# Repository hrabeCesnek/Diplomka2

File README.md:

# Diplomka
Nothing more than destiny fullfillation

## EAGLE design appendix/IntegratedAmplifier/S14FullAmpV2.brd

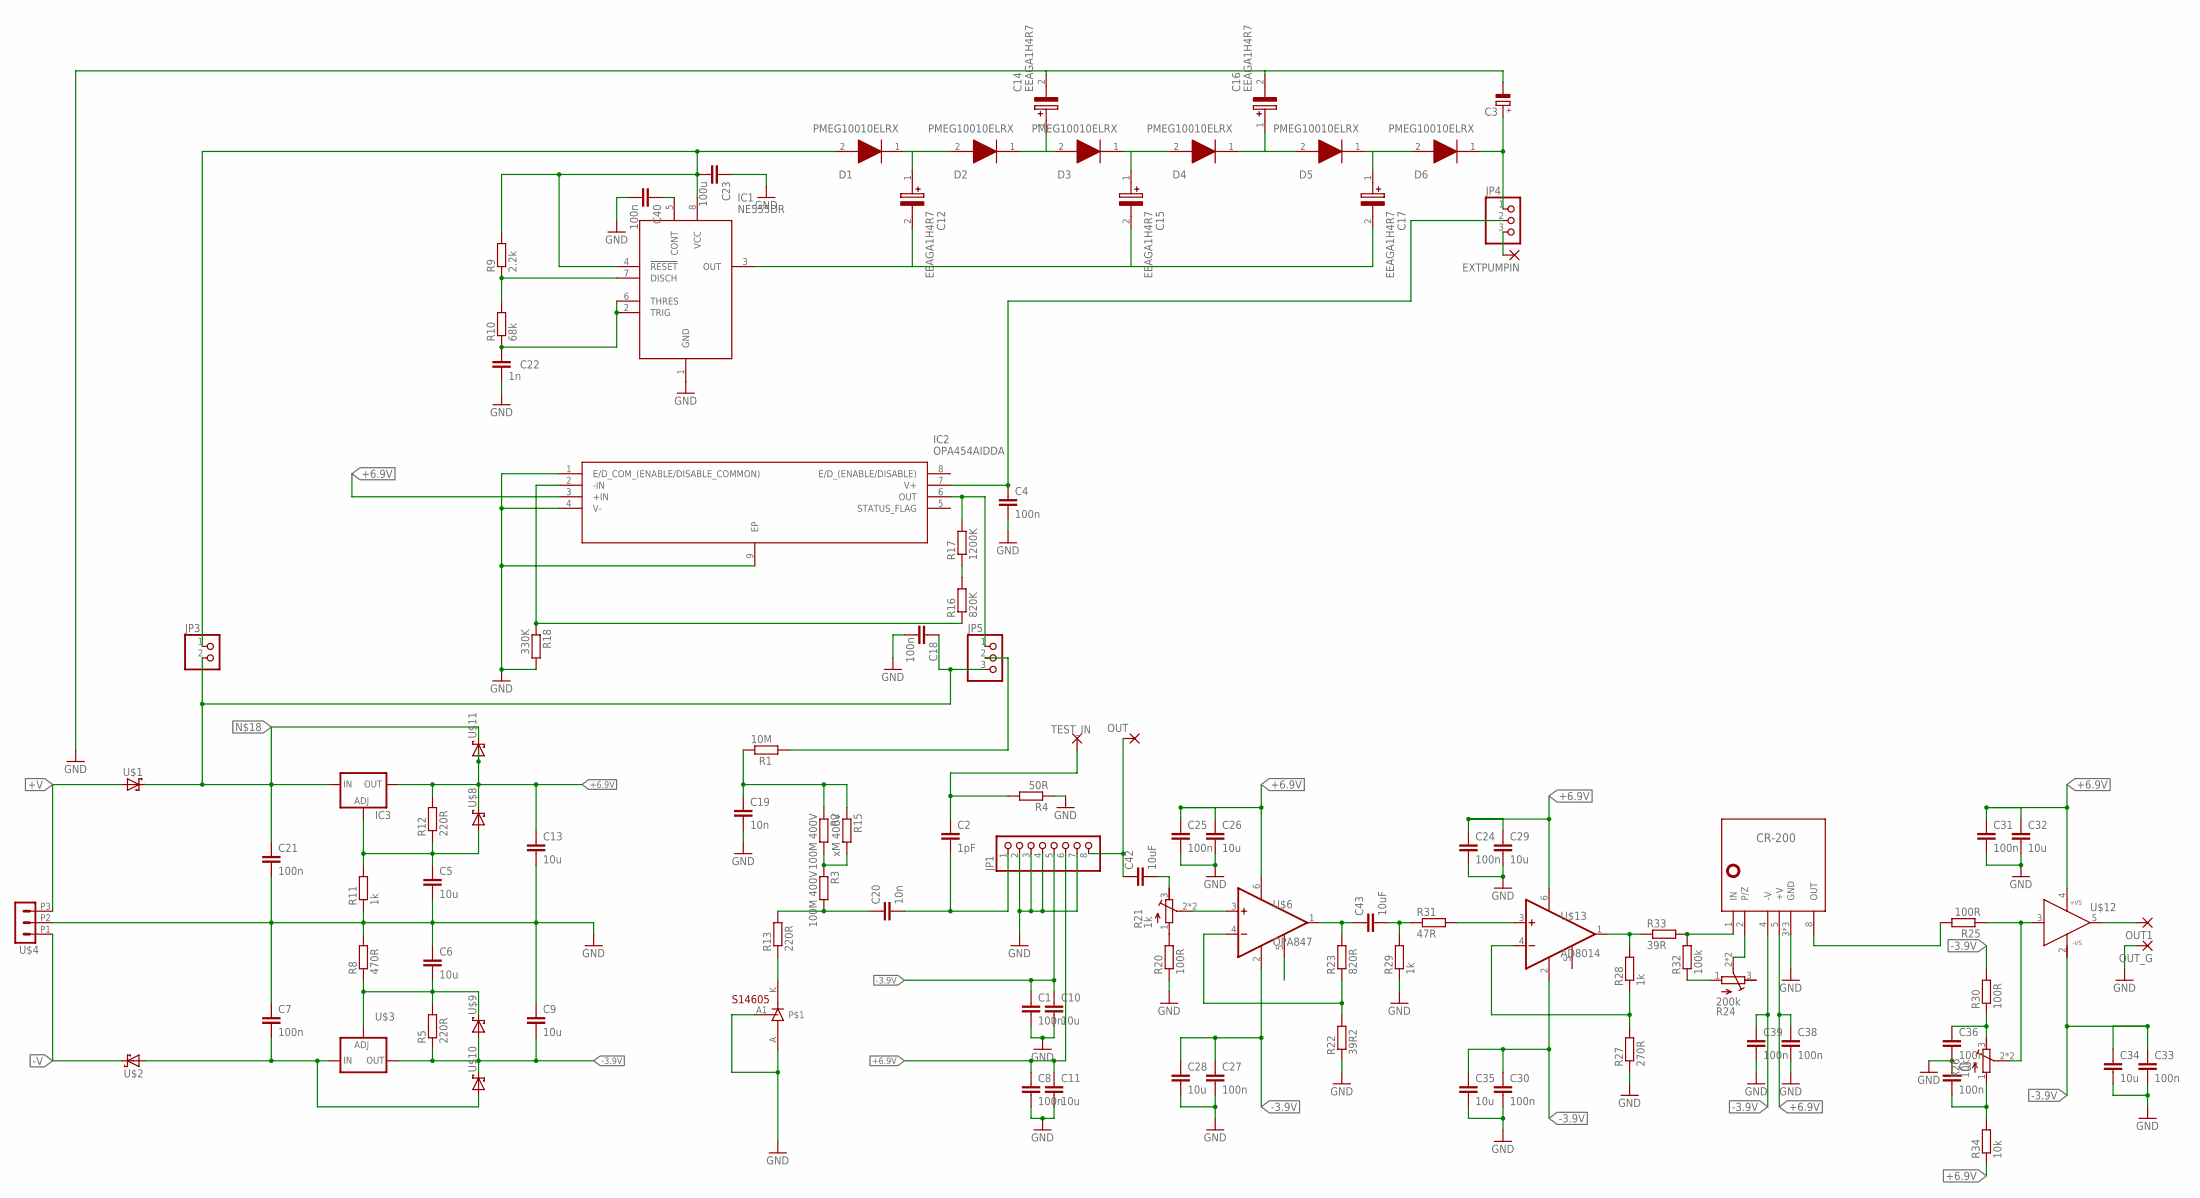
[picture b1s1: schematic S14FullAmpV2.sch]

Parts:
C1, C4, C7, C8, C18, C21, C24, C25, C27, C30, C31, C33, C36, C37, C38, C39, C40: 100n; C0603
C2: 1pF; C0603
C3: CPOL-EUE3.5-8; E3,5-8
C5, C6, C9, C10, C11, C13, C26, C28, C29, C32, C34, C35: 10u; C0805
C12, C14, C15, C16, C17: EEAGA1H4R7; CAPPRD150W50D400H800
C19, C20: 10n; C0603
C22: 1n; C0603
C23: 100u; C0603
C42, C43: 10uF; C0805
CR-200: CR-200H; CR-XXX-H
D1, D2, D3, D4, D5, D6: PMEG10010ELRX; SODFL3517X110N
EXTPUMPIN: 1,6/0,9
IC1: NE555DR; SOIC127P600X175-8N
IC2: OPA454AIDDA; SOIC127P600X170-9N
IC3: LM317; SO-08
JP1: HEADER-1X8ROUND; 1X08_ROUND
JP3: PINHD-1X2; 1X02
JP4, JP5: PINHD-1X3; 1X03
OUT: 1,6/0,9
OUT1: 2,54/0,9
OUT_G: 2,54/0,9
R1: 10M; M0805
R2, R3: 100M 400V; M1206
R4: 50R; R0805
R5, R12: 220R; R0603
R8: 470R; R0603
R9: 2.2k; R0805
R10: 68k; R0805
R11, R28, R29: 1k; R0603
R13: 220R; R0805
R15: xM 400V; M1206
R16: 820K; R0805
R17: 1200K; R0805
R18: 330K; R0805
R20, R25, R30: 100R; R0603
R21: 1k; RTRIM3299W
R22: 39R2; R0603
R23: 820R; R0603
R24: 200k; RTRIM3299W
R26: 10k; RTRIM3299W
R27: 270R; R0603
R31: 47R; R0603
R32: 100k; R0603
R33: 39R; R0603
R34: 10k; R0603
S1: S14605; RHDR3W53P0X254_1X3_762X246X425
TEST_IN: 1,6/0,9
U$1, U$2, U$8, U$9, U$10, U$11: BAS383; MICROMELF-R
U$3: LM337-SO8; SO8
U$4: XHT03T; XHT03
U$6: OPA847; SOT23-6
U$12: MAX4201; SOT23-5
U$13: AD8014; SOT23-6

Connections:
+6.9V: C8.1, C11.1, C13.1, C24.1, C25.1, C26.1, C29.1, C31.1, C32.1, C38.1, CR-200.5 (+V), IC2.3 (+IN), IC3.2 (OUT), IC3.3 (OUT), IC3.6 (OUT), IC3.7 (OUT), JP1.6, R12.2, R34.1, U$6.6 (V+), U$8.C, U$11.A, U$12.4 (+VS), U$13.6 (V+)
+V: U$1.A, U$4.P3 (3)
-3.9V: C1.1, C9.2, C10.1, C27.1, C28.1, C30.1, C33.1, C34.1, C35.1, C39.1, CR-200.4 (-V), JP1.5, R5.1, R30.2, U$3.1 (OUT), U$6.2 (V-), U$9.A, U$10.C, U$12.2 (-VS), U$13.2 (V-)
-V: U$2.C, U$4.P1 (1)
GND: C1.2, C3.-, C4.2, C5.2, C6.1, C7.1, C8.2, C9.1, C10.2, C11.2, C13.2, C14.2 (-), C16.2 (-), C18.2, C19.2, C21.2, C22.2, C23.1, C24.2, C25.2, C26.2, C27.2, C28.2, C29.2, C30.2, C31.2, C32.2, C33.2, C34.2, C35.2, C36.2, C37.1, C38.2, C39.2, C40.2, CR-200.3 (GND), CR-200.6 (GND), CR-200.7 (GND), IC1.1 (GND), IC2.1 (E/D_COM_(ENABLE/DISABLE_COMMON)), IC2.4 (V-), IC2.9 (EP), JP1.2, JP1.3, JP1.4, JP1.7, OUT_G.1, R4.1, R8.2, R11.1, R18.2, R20.1, R22.1, R27.1, R29.1, S1.A (ANODE), S1.A1, U$4.P2 (2)
unnamed: C19.1, R1.2, R2.1, R15.1
unnamed: JP5.2, R1.1
unnamed: R2.2, R3.1, R15.2
unnamed: C20.1, R3.2, R13.2
unnamed: C2.2, C20.2, JP1.1
unnamed: C2.1, R4.2, TEST_IN.1
unnamed: C42.1, JP1.8, OUT.1
unnamed: R24.1 (A), R32.1
unnamed: EXTPUMPIN.1, JP4.3
unnamed: C23.2, D1.2 (A), IC1.4 (!RESET), IC1.8 (VCC), JP3.1, R9.2
unnamed: C6.2, R5.2, R8.1, U$3.4 (ADJ), U$9.C
unnamed: R13.1, S1.K (KATHODE)
unnamed: C5.1, IC3.4 (ADJ), R11.2, R12.1, U$8.A
unnamed: R16.2, R17.1
unnamed: C12.1 (+), D1.1 (K), D2.2 (A)
unnamed: C12.2 (-), C15.2 (-), C17.2 (-), IC1.3 (OUT)
unnamed: C18.1, C21.1, IC3.1 (IN), JP3.2, JP5.3, U$1.C, U$11.C
unnamed: C14.1 (+), D2.1 (K), D3.2 (A)
unnamed: C40.1, IC1.5 (CONT)
unnamed: C3.+, D6.1 (K), JP4.1
unnamed: C15.1 (+), D3.1 (K), D4.2 (A)
unnamed: C16.1 (+), D4.1 (K), D5.2 (A)
unnamed: R20.2, R21.1 (A)
unnamed: C17.1 (+), D5.1 (K), D6.2 (A)
unnamed: C42.2, R21.3 (E)
unnamed: IC1.7 (DISCH), R9.1, R10.2
unnamed: C22.1, IC1.2 (TRIG), IC1.6 (THRES), R10.1
unnamed: IC2.6 (OUT), JP5.1, R17.2
unnamed: IC2.2 (-IN), R16.1, R18.1
unnamed: R22.2, R23.1, U$6.4 (-IN)
unnamed: R21.2 (S), R21.4 (S), U$6.3 (+IN)
unnamed: R25.1, R26.2 (S), R26.4 (S), U$12.3 (IN)
unnamed: OUT1.1, U$12.5 (OUT)
unnamed: R27.2, R28.1, U$13.4 (-IN)
unnamed: CR-200.1 (IN), R32.2, R33.2
unnamed: R31.2, U$13.3 (+IN)
unnamed: C36.1, R26.3 (E), R30.1
unnamed: CR-200.2 (P/Z), R24.2 (S), R24.4 (S)
unnamed: C43.1, R23.2, U$6.1 (OUT)
unnamed: C43.2, R29.2, R31.1
unnamed: C4.1, IC2.7 (V+), JP4.2
unnamed: R28.2, R33.1, U$13.1 (OUT)
unnamed: C37.2, R26.1 (A), R34.2
unnamed: CR-200.8 (OUT), R25.2
SH: U$13.5 (SH)
V-: C7.2, U$2.A, U$3.2 (IN), U$3.3 (IN), U$3.6 (IN), U$3.7 (IN), U$10.A

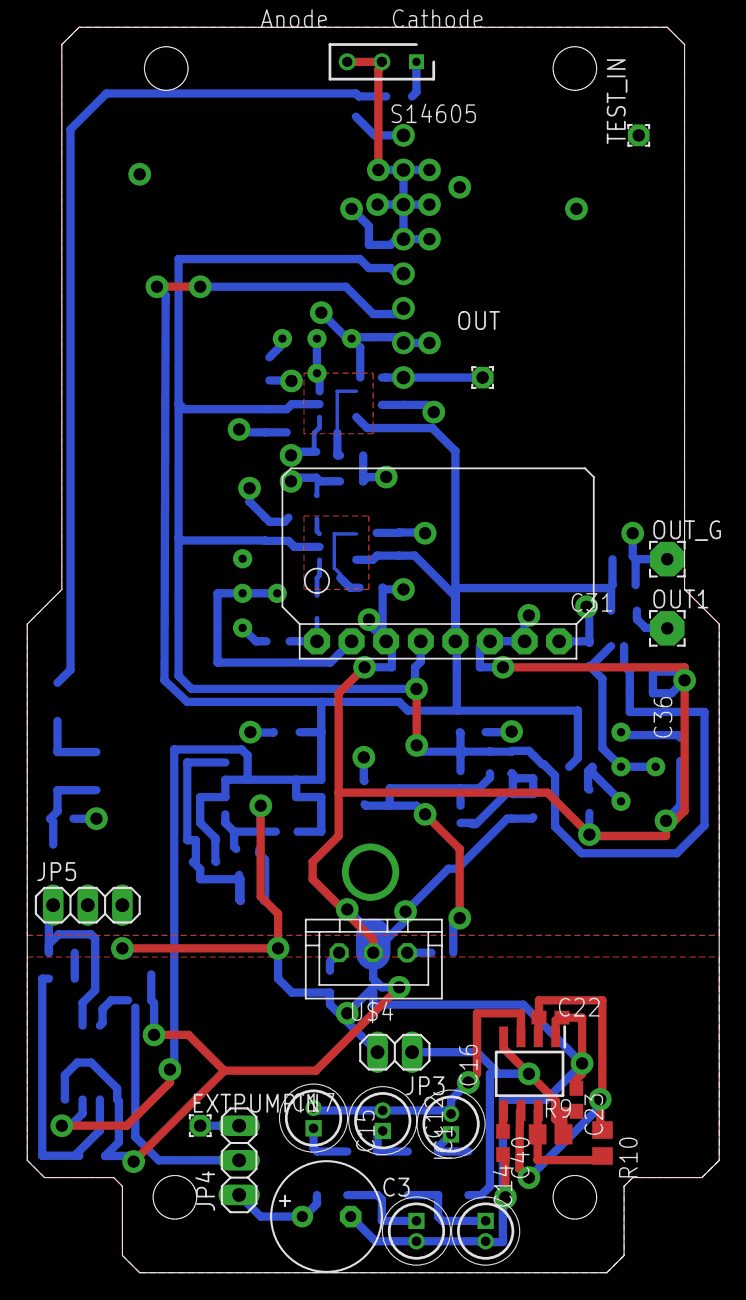
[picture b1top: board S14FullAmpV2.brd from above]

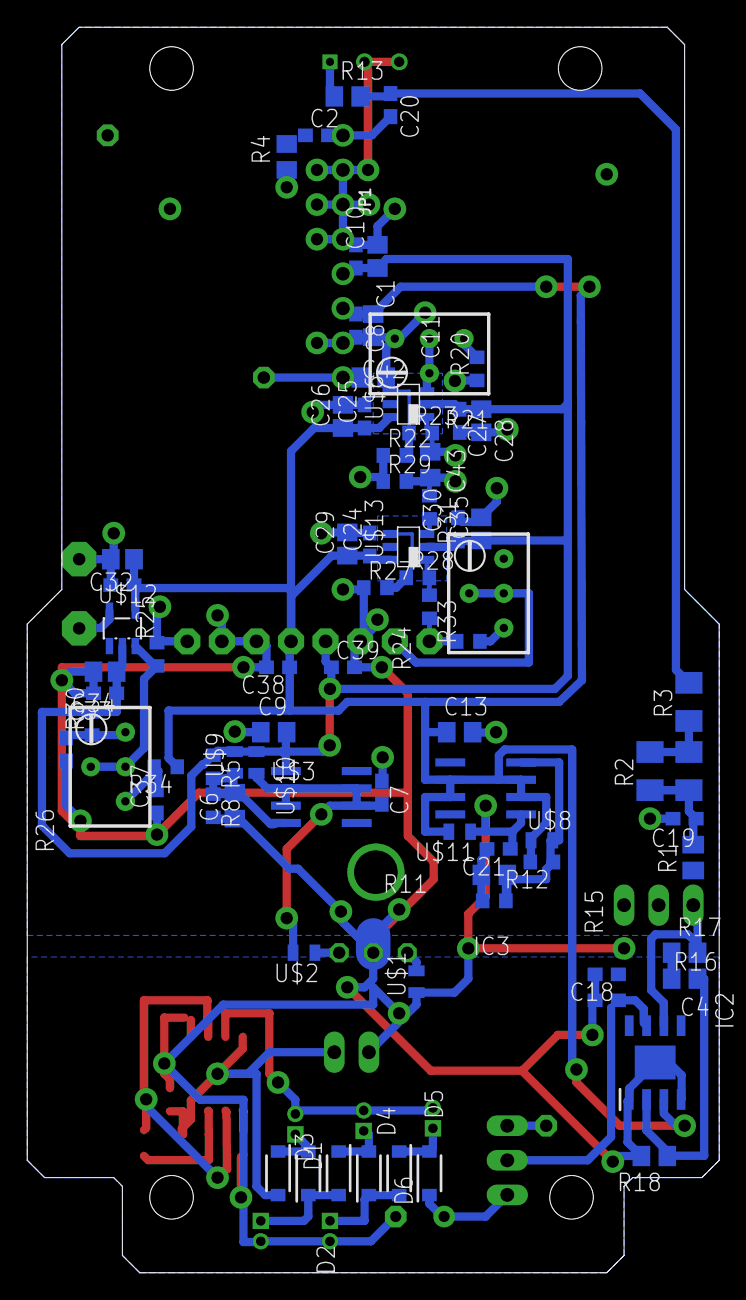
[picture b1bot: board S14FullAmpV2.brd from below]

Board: 2 copper layers, 50.8 x 91.4 mm, 103 parts (80 on the bottom side), 50 nets.

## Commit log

2024-05-10 finals8
2024-05-10 finalising
2024-05-14 final final

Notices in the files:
parts and their libraries:
microbuilder: This work is placed in the public domain, and may be freely used for commercial and non-commercial work with the following conditions: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
Connectors: Copyright (C) PaJa 2011
